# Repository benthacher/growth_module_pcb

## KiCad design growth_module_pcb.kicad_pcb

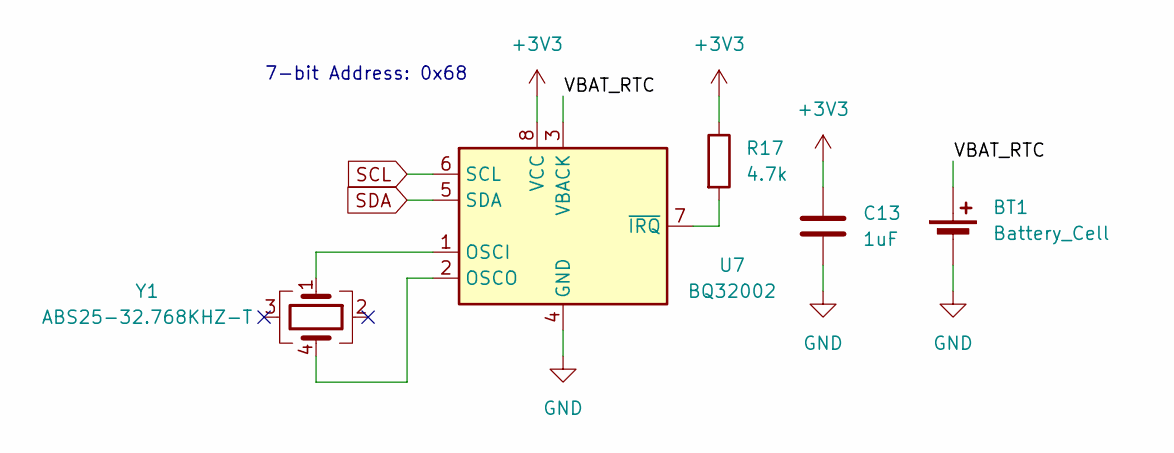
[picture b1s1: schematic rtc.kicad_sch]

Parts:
BT1: Battery_Cell; BatteryHolder_Keystone_3000_1x12mm
C13: 1uF; C_0603_1608Metric_Pad1.08x0.95mm_HandSolder
R17: 4.7k; R_0603_1608Metric_Pad0.98x0.95mm_HandSolder
U7: BQ32002; SOIC-8_3.9x4.9mm_P1.27mm
Y1: ABS25-32.768KHZ-T; Crystal_SMD_Abracon_ABS25-4Pin_8.0x3.8mm

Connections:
+3V3: C13.1, R17.1, U7.8 (VCC); also elsewhere on the board
/RTC/VBAT_RTC: BT1.1 (+), U7.3 (VBACK)
GND: BT1.2 (-), C13.2, U7.4 (GND); also elsewhere on the board
unnamed: U7.1 (OSCI), Y1.1
unnamed: U7.2 (OSCO), Y1.4
unnamed: R17.2, U7.7 (~IRQ)
SCL: U7.6 (SCL); also elsewhere on the board
SDA: U7.5 (SDA); also elsewhere on the board

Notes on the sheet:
7-bit Address: 0x68

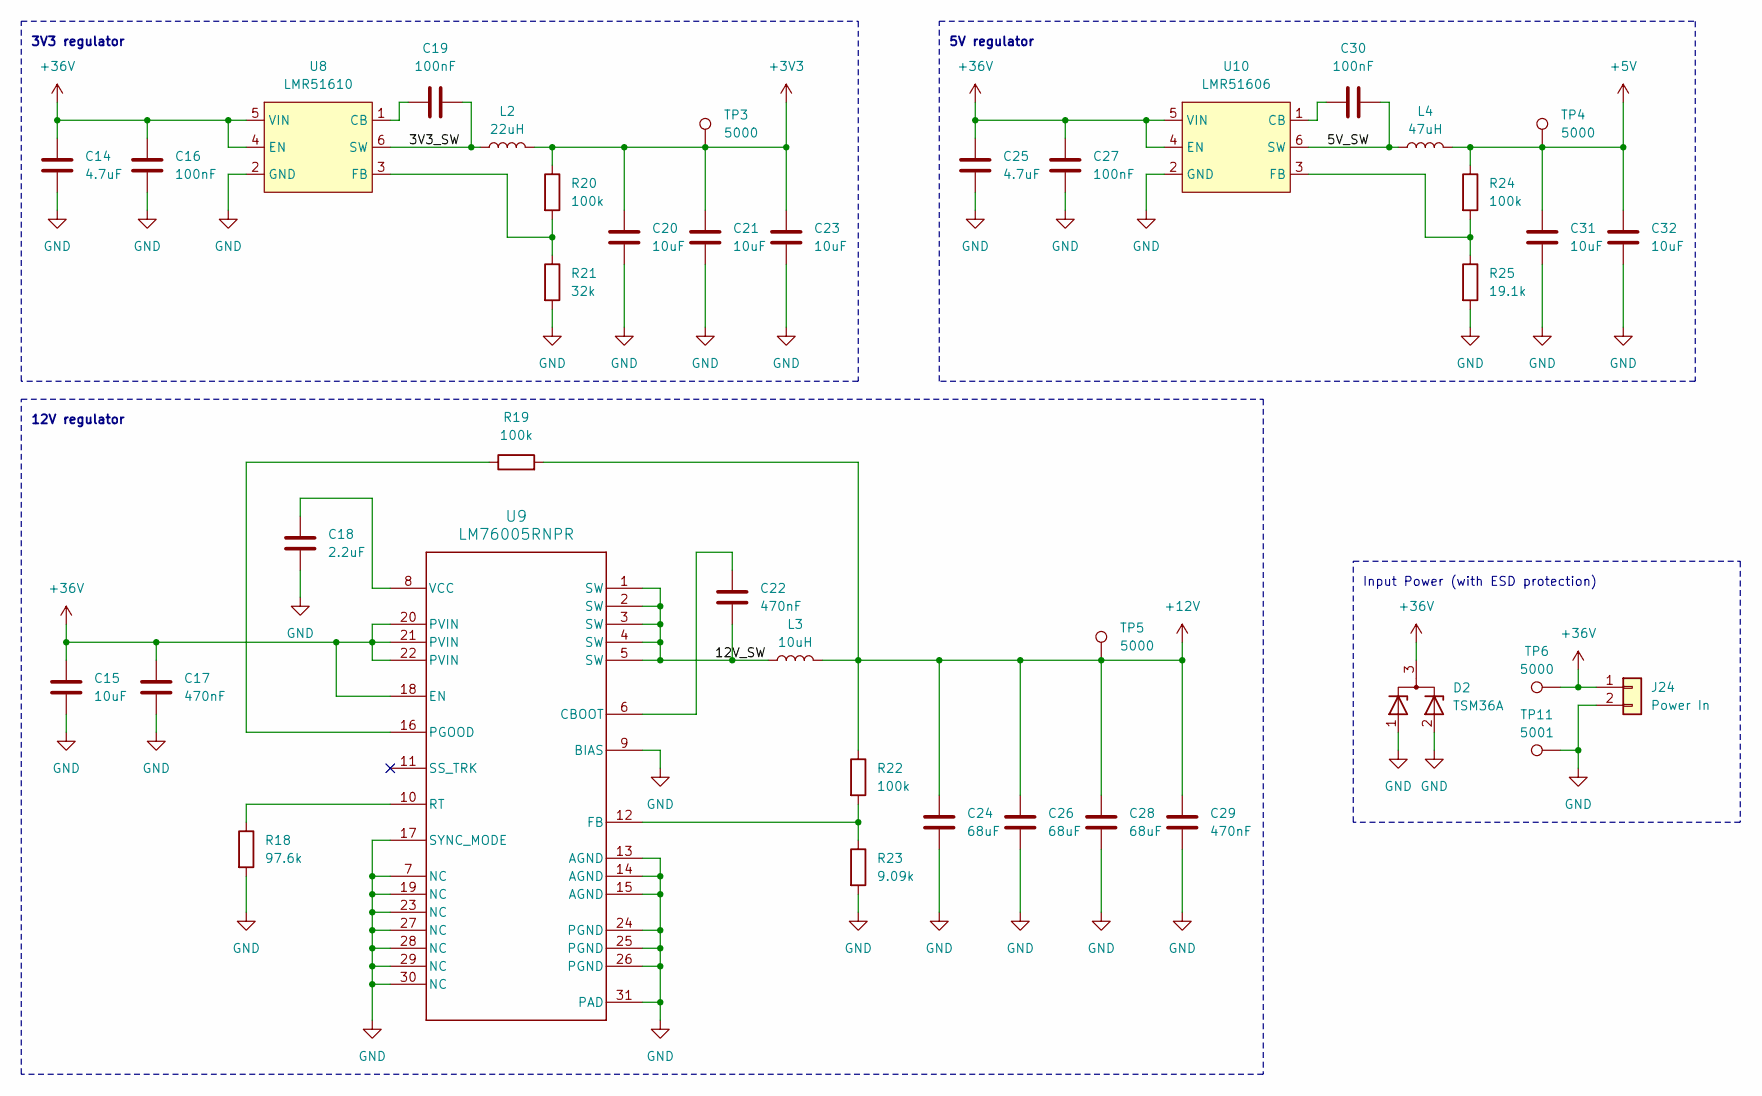
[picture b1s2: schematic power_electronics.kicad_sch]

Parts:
C14, C25: 4.7uF; C_2220_5750Metric_Pad1.97x5.40mm_HandSolder
C15: 10uF; C_1210_3225Metric_Pad1.33x2.70mm_HandSolder
C16, C19, C27, C30: 100nF; C_0603_1608Metric_Pad1.08x0.95mm_HandSolder
C17: 470nF; C_0805_2012Metric_Pad1.18x1.45mm_HandSolder
C18: 2.2uF; C_0603_1608Metric_Pad1.08x0.95mm_HandSolder
C20, C21, C23, C31, C32: 10uF; C_0805_2012Metric_Pad1.18x1.45mm_HandSolder
C22, C29: 470nF; C_0603_1608Metric_Pad1.08x0.95mm_HandSolder
C24, C26, C28: 68uF; CP_Elec_6.3x7.7
D2: TSM36A; SOT-23_Handsoldering
J24: Power In; JST_VH_S2P-VH_1x02_P3.96mm_Horizontal
L2: 22uH; SDR1006220ML
L3: 10uH; IND_BOURNS_SRP1270-M
L4: 47uH; SDR1006220ML
R18: 97.6k; R_0603_1608Metric_Pad0.98x0.95mm_HandSolder
R19, R20, R22, R24: 100k; R_0603_1608Metric_Pad0.98x0.95mm_HandSolder
R21: 32k; R_0603_1608Metric_Pad0.98x0.95mm_HandSolder
R23: 9.09k; R_0603_1608Metric_Pad0.98x0.95mm_HandSolder
R25: 19.1k; R_0603_1608Metric_Pad0.98x0.95mm_HandSolder
TP3, TP4, TP5, TP6: 5000; TestPoint_Keystone_5000-5004_Miniature
TP11: 5001; TestPoint_Keystone_5000-5004_Miniature
U8: LMR51610; LMR51610XDBVR
U9: LM76005RNPR; RNP0030A
U10: LMR51606; LMR51610XDBVR

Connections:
+3V3: C20.1, C21.1, C23.1, L2.2, R20.1, TP3.1; also elsewhere on the board
+5V: C31.1, C32.1, L4.2, R24.1, TP4.1; also elsewhere on the board
+12V: C24.1, C26.1, C28.1, C29.1, L3.2, R19.2, R22.1, TP5.1; also elsewhere on the board
+36V: C14.1, C15.1, C16.1, C17.1, C25.1, C27.1, D2.3 (A), J24.1, TP6.1, U8.4 (EN), U8.5 (VIN), U9.18 (EN), U9.20 (PVIN), U9.21 (PVIN), U9.22 (PVIN), U10.4 (EN), U10.5 (VIN); also elsewhere on the board
/Power electronics/3V3_SW: C19.2, L2.1, U8.6 (SW)
/Power electronics/5V_SW: C30.2, L4.1, U10.6 (SW)
/Power electronics/12V_SW: C22.2, L3.1, U9.1 (SW), U9.2 (SW), U9.3 (SW), U9.4 (SW), U9.5 (SW)
GND: C14.2, C15.2, C16.2, C17.2, C18.2, C20.2, C21.2, C23.2, C24.2, C25.2, C26.2, C27.2, C28.2, C29.2, C31.2, C32.2, D2.1 (K), D2.2 (K), J24.2, R18.2, R21.2, R23.2, R25.2, TP11.1, U8.2 (GND), U9.7 (NC), U9.9 (BIAS), U9.13 (AGND), U9.14 (AGND), U9.15 (AGND), U9.17 (SYNC_MODE), U9.19 (NC), U9.23 (NC), U9.24 (PGND), U9.25 (PGND), U9.26 (PGND), U9.27 (NC), U9.28 (NC), U9.29 (NC), U9.30 (NC), U9.31 (PAD), U10.2 (GND); also elsewhere on the board
unnamed: C19.1, U8.1 (CB)
unnamed: R20.2, R21.1, U8.3 (FB)
unnamed: C22.1, U9.6 (CBOOT)
unnamed: R22.2, R23.1, U9.12 (FB)
unnamed: R19.1, U9.16 (PGOOD)
unnamed: R18.1, U9.10 (RT)
unnamed: C18.1, U9.8 (VCC)
unnamed: C30.1, U10.1 (CB)
unnamed: R24.2, R25.1, U10.3 (FB)

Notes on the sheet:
Input Power (with ESD protection)
12V regulator
5V regulator
3V3 regulator

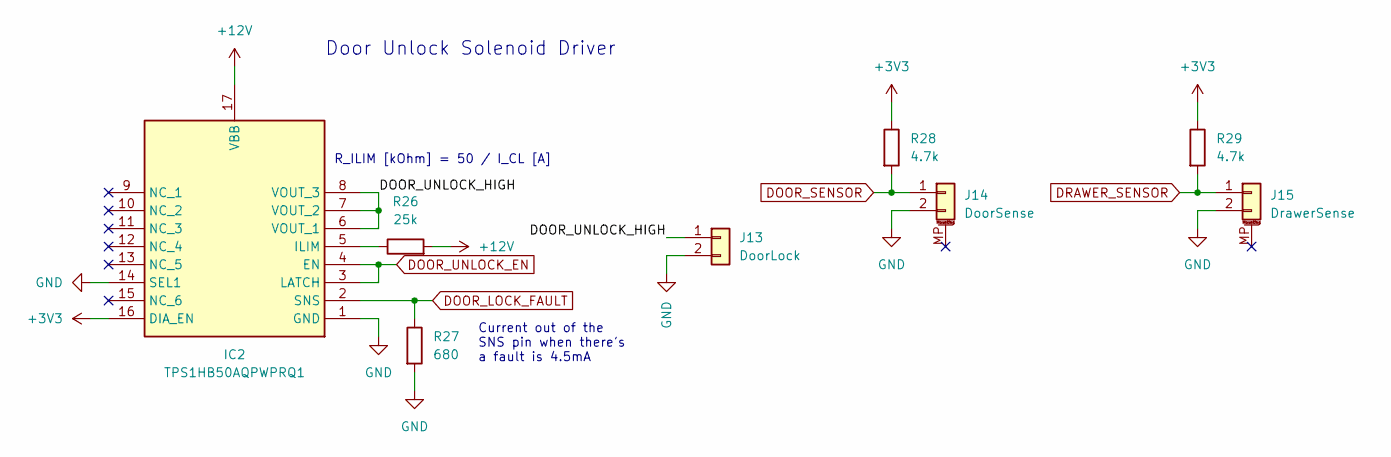
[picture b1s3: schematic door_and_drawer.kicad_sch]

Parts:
IC2: TPS1HB50AQPWPRQ1; HTSSOP-16-1EP_4.4x5mm_P0.65mm_EP3.4x5mm_Mask3x3mm_ThermalVi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; Manufacturer_Part_Number TPS1HB50AQPWPRQ1; Mouser Part Number 595-TPS1HB50AQPWPRQ1
J13: DoorLock; JST_XA_S02B-XASK-1_1x02_P2.50mm_Horizontal
J14: DoorSense; JST_SH_SM02B-SRSS-TB_1x02-1MP_P1.00mm_Horizontal
J15: DrawerSense; JST_SH_SM02B-SRSS-TB_1x02-1MP_P1.00mm_Horizontal
R26: 25k; R_0603_1608Metric_Pad0.98x0.95mm_HandSolder
R27: 680; R_0603_1608Metric_Pad0.98x0.95mm_HandSolder
R28, R29: 4.7k; R_0603_1608Metric_Pad0.98x0.95mm_HandSolder

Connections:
+3V3: IC2.16 (DIA_EN), R28.1, R29.1; also elsewhere on the board
+12V: IC2.17 (VBB), R26.2; also elsewhere on the board
/Door and Drawer/DOOR_UNLOCK_HIGH: IC2.6 (VOUT_1), IC2.7 (VOUT_2), IC2.8 (VOUT_3), J13.1
DOOR_LOCK_FAULT: IC2.2 (SNS), R27.1; also elsewhere on the board
DOOR_SENSOR: J14.1, R28.2; also elsewhere on the board
DOOR_UNLOCK_EN: IC2.3 (LATCH), IC2.4 (EN); also elsewhere on the board
DRAWER_SENSOR: J15.1, R29.2; also elsewhere on the board
GND: IC2.1 (GND), IC2.14 (SEL1), J13.2, J14.2, J15.2, R27.2; also elsewhere on the board
unnamed: IC2.5 (ILIM), R26.1

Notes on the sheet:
R_ILIM [kOhm] = 50 / I_CL [A]
Door Unlock Solenoid Driver
Current out of the SNS pin when there's a fault is 4.5mA

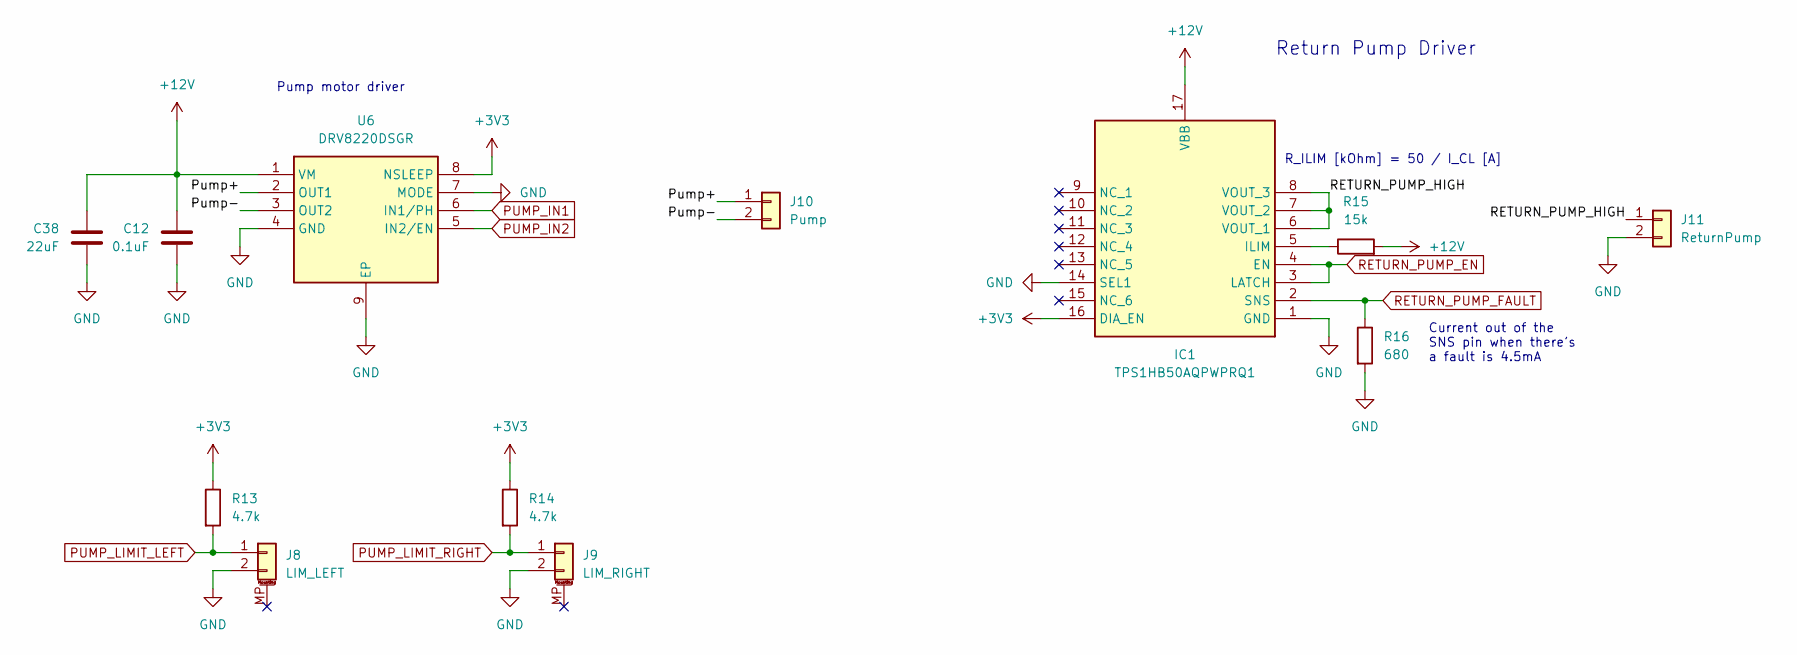
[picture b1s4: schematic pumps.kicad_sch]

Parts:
C12: 0.1uF; C_0603_1608Metric_Pad1.08x0.95mm_HandSolder
C38: 22uF; C_0805_2012Metric_Pad1.18x1.45mm_HandSolder
IC1: TPS1HB50AQPWPRQ1; HTSSOP-16-1EP_4.4x5mm_P0.65mm_EP3.4x5mm_Mask3x3mm_ThermalVi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; Manufacturer_Part_Number TPS1HB50AQPWPRQ1; Mouser Part Number 595-TPS1HB50AQPWPRQ1
J8: LIM_LEFT; JST_SH_SM02B-SRSS-TB_1x02-1MP_P1.00mm_Horizontal
J9: LIM_RIGHT; JST_SH_SM02B-SRSS-TB_1x02-1MP_P1.00mm_Horizontal
J10: Pump; JST_XA_S02B-XASK-1_1x02_P2.50mm_Horizontal
J11: ReturnPump; JST_XA_S02B-XASK-1_1x02_P2.50mm_Horizontal
R13, R14: 4.7k; R_0603_1608Metric_Pad0.98x0.95mm_HandSolder
R15: 15k; R_0603_1608Metric_Pad0.98x0.95mm_HandSolder
R16: 680; R_0603_1608Metric_Pad0.98x0.95mm_HandSolder
U6: DRV8220DSGR; SON50P200X200X80-9N; Manufacturer_Part_Number DRV8220DSGR; Mouser Part Number 595-DRV8220DSGR

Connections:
+3V3: IC1.16 (DIA_EN), R13.1, R14.1, U6.8 (NSLEEP); also elsewhere on the board
+12V: C12.1, C38.1, IC1.17 (VBB), R15.2, U6.1 (VM); also elsewhere on the board
/Pumps/Pump+: J10.1, U6.2 (OUT1)
/Pumps/Pump-: J10.2, U6.3 (OUT2)
/Pumps/RETURN_PUMP_HIGH: IC1.6 (VOUT_1), IC1.7 (VOUT_2), IC1.8 (VOUT_3), J11.1
GND: C12.2, C38.2, IC1.1 (GND), IC1.14 (SEL1), J8.2, J9.2, J11.2, R16.2, U6.4 (GND), U6.7 (MODE), U6.9 (EP); also elsewhere on the board
unnamed: IC1.5 (ILIM), R15.1
PUMP_IN1: U6.6 (IN1/PH); also elsewhere on the board
PUMP_IN2: U6.5 (IN2/EN); also elsewhere on the board
PUMP_LIMIT_LEFT: J8.1, R13.2; also elsewhere on the board
PUMP_LIMIT_RIGHT: J9.1, R14.2; also elsewhere on the board
RETURN_PUMP_EN: IC1.3 (LATCH), IC1.4 (EN); also elsewhere on the board
RETURN_PUMP_FAULT: IC1.2 (SNS), R16.1; also elsewhere on the board

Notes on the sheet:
R_ILIM [kOhm] = 50 / I_CL [A]
Current out of the SNS pin when there's a fault is 4.5mA
Return Pump Driver
Pump motor driver

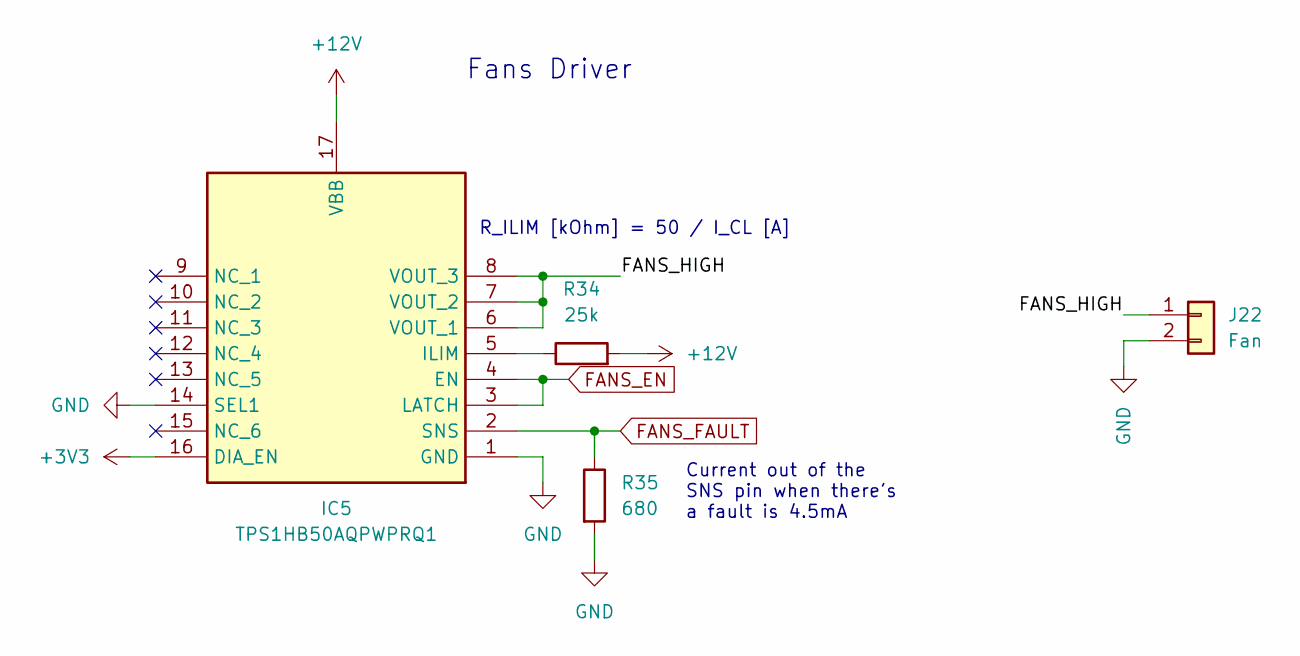
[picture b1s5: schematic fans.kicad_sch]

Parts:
IC5: TPS1HB50AQPWPRQ1; HTSSOP-16-1EP_4.4x5mm_P0.65mm_EP3.4x5mm_Mask3x3mm_ThermalVi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; Manufacturer_Part_Number TPS1HB50AQPWPRQ1; Mouser Part Number 595-TPS1HB50AQPWPRQ1
J22: Fan; JST_XA_S02B-XASK-1_1x02_P2.50mm_Horizontal
R34: 25k; R_0603_1608Metric_Pad0.98x0.95mm_HandSolder
R35: 680; R_0603_1608Metric_Pad0.98x0.95mm_HandSolder

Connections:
+3V3: IC5.16 (DIA_EN); also elsewhere on the board
+12V: IC5.17 (VBB), R34.2; also elsewhere on the board
/Fans/FANS_HIGH: IC5.6 (VOUT_1), IC5.7 (VOUT_2), IC5.8 (VOUT_3), J22.1
FANS_EN: IC5.3 (LATCH), IC5.4 (EN); also elsewhere on the board
FANS_FAULT: IC5.2 (SNS), R35.1; also elsewhere on the board
GND: IC5.1 (GND), IC5.14 (SEL1), J22.2, R35.2; also elsewhere on the board
unnamed: IC5.5 (ILIM), R34.1

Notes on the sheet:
R_ILIM [kOhm] = 50 / I_CL [A]
Current out of the SNS pin when there's a fault is 4.5mA
Fans Driver

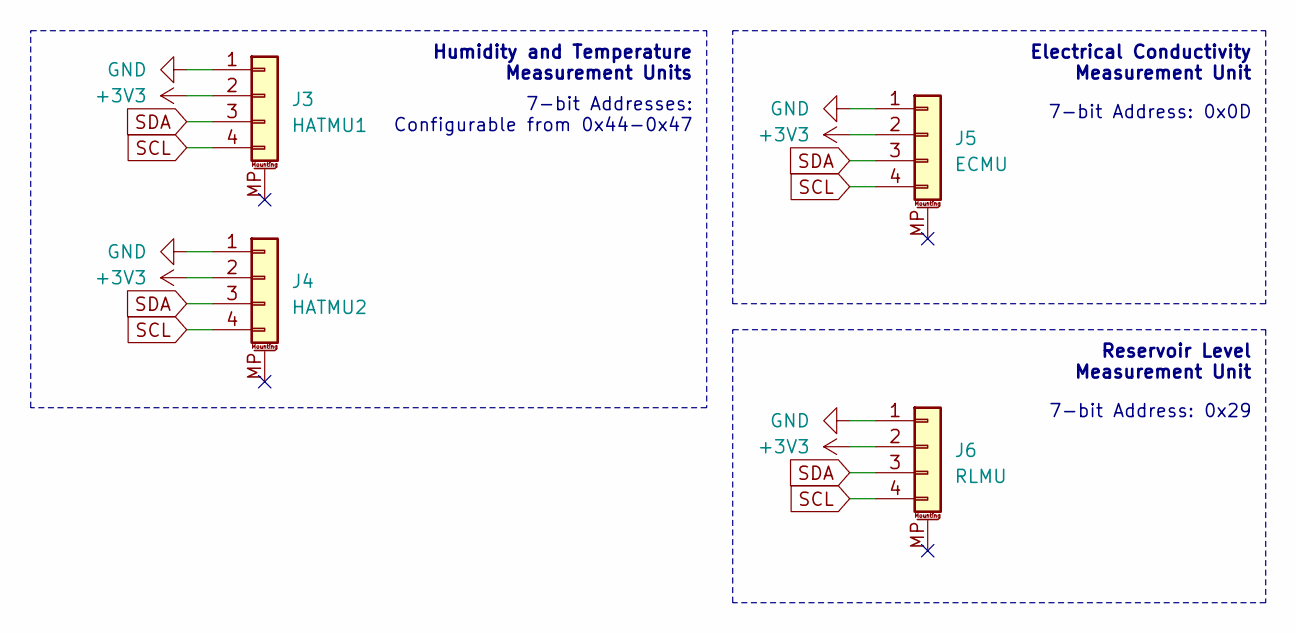
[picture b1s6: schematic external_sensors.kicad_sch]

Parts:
J3: HATMU1; JST_SH_SM04B-SRSS-TB_1x04-1MP_P1.00mm_Horizontal
J4: HATMU2; JST_SH_SM04B-SRSS-TB_1x04-1MP_P1.00mm_Horizontal
J5: ECMU; JST_SH_SM04B-SRSS-TB_1x04-1MP_P1.00mm_Horizontal
J6: RLMU; JST_SH_SM04B-SRSS-TB_1x04-1MP_P1.00mm_Horizontal

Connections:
+3V3: J3.2, J4.2, J5.2, J6.2; also elsewhere on the board
GND: J3.1, J4.1, J5.1, J6.1; also elsewhere on the board
SCL: J3.4, J4.4, J5.4, J6.4; also elsewhere on the board
SDA: J3.3, J4.3, J5.3, J6.3; also elsewhere on the board

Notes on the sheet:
Reservoir Level Measurement Unit
7-bit Addresses: Configurable from 0x44-0x47
Electrical Conductivity Measurement Unit
Humidity and Temperature Measurement Units
7-bit Address: 0x29
7-bit Address: 0x0D

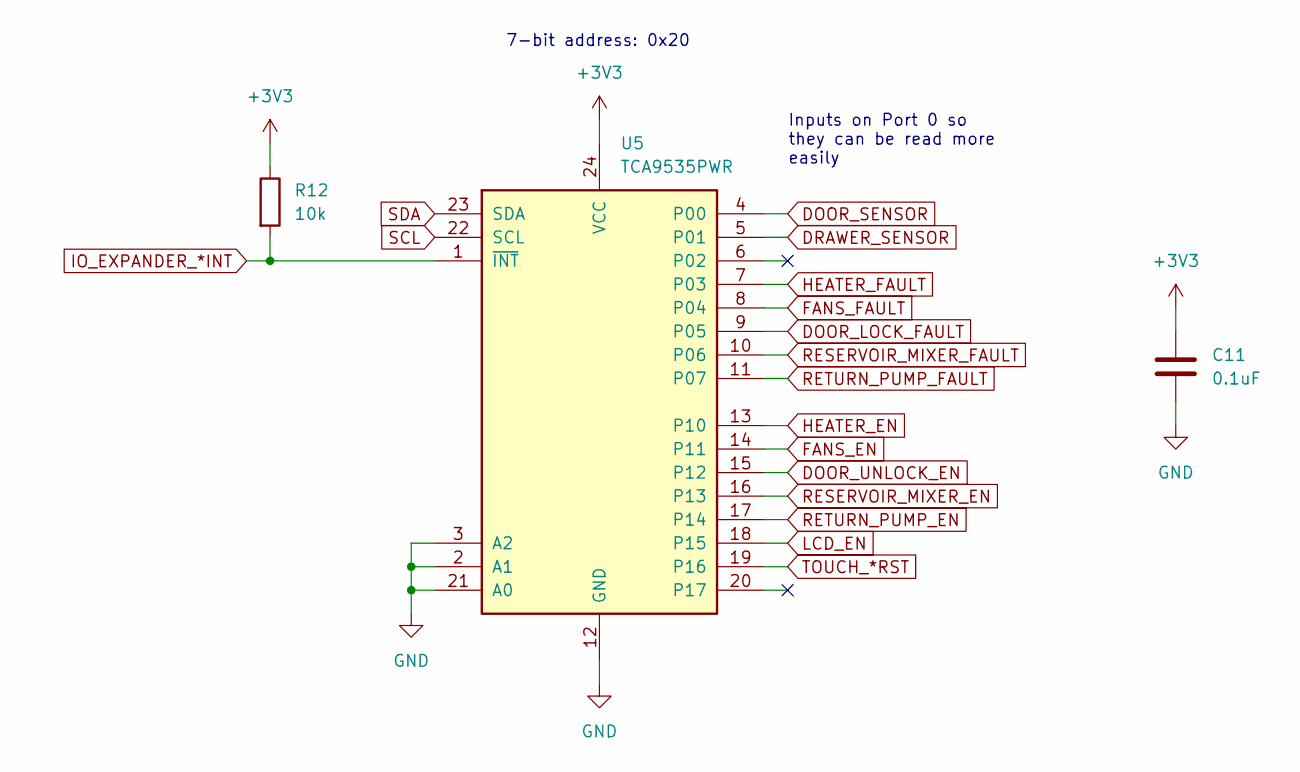
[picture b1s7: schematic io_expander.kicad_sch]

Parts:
C11: 0.1uF; C_0603_1608Metric_Pad1.08x0.95mm_HandSolder
R12: 10k; R_0603_1608Metric_Pad0.98x0.95mm_HandSolder
U5: TCA9535PWR; TSSOP-24_4.4x7.8mm_P0.65mm

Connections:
+3V3: C11.1, R12.1, U5.24 (VCC); also elsewhere on the board
DOOR_LOCK_FAULT: U5.9 (P05); also elsewhere on the board
DOOR_SENSOR: U5.4 (P00); also elsewhere on the board
DOOR_UNLOCK_EN: U5.15 (P12); also elsewhere on the board
DRAWER_SENSOR: U5.5 (P01); also elsewhere on the board
FANS_EN: U5.14 (P11); also elsewhere on the board
FANS_FAULT: U5.8 (P04); also elsewhere on the board
GND: C11.2, U5.2 (A1), U5.3 (A2), U5.12 (GND), U5.21 (A0); also elsewhere on the board
HEATER_EN: U5.13 (P10); also elsewhere on the board
HEATER_FAULT: U5.7 (P03); also elsewhere on the board
IO_EXPANDER_*INT: R12.2, U5.1 (~INT); also elsewhere on the board
LCD_EN: U5.18 (P15); also elsewhere on the board
RESERVOIR_MIXER_EN: U5.16 (P13); also elsewhere on the board
RESERVOIR_MIXER_FAULT: U5.10 (P06); also elsewhere on the board
RETURN_PUMP_EN: U5.17 (P14); also elsewhere on the board
RETURN_PUMP_FAULT: U5.11 (P07); also elsewhere on the board
SCL: U5.22 (SCL); also elsewhere on the board
SDA: U5.23 (SDA); also elsewhere on the board
TOUCH_*RST: U5.19 (P16); also elsewhere on the board

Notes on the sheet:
7-bit address: 0x20
Inputs on Port 0 so they can be read more easily

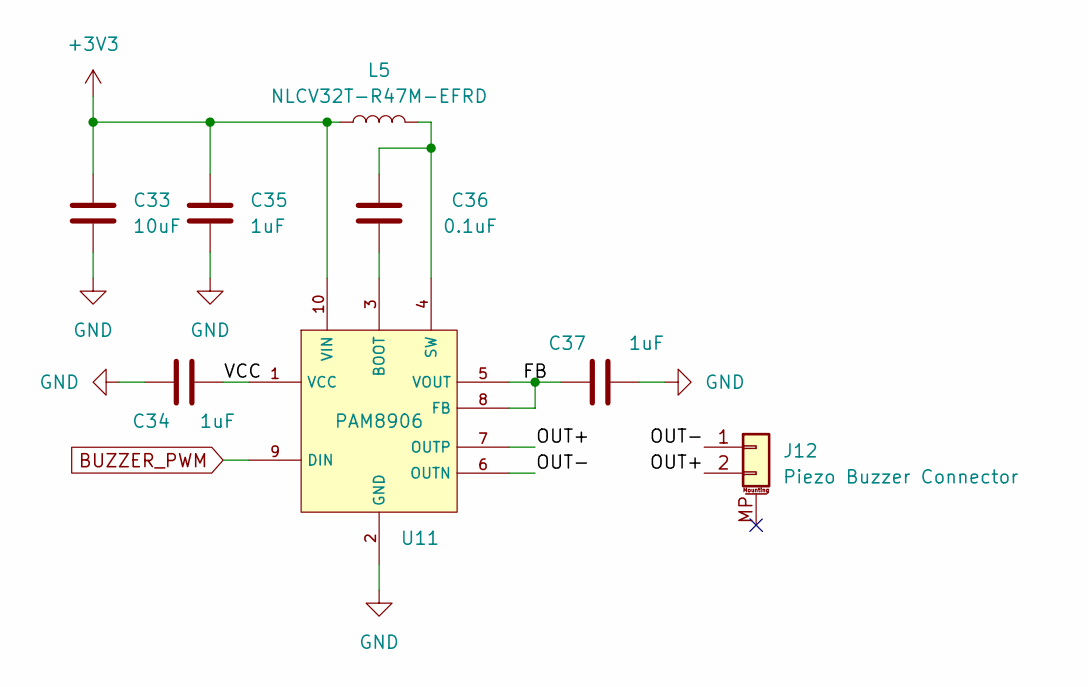
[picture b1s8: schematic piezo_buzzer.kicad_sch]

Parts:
C33: 10uF; C_0805_2012Metric_Pad1.18x1.45mm_HandSolder
C34, C35, C37: 1uF; C_0603_1608Metric_Pad1.08x0.95mm_HandSolder
C36: 0.1uF; C_0603_1608Metric_Pad1.08x0.95mm_HandSolder
J12: Piezo Buzzer Connector; JST_PH_S2B-PH-SM4-TB_1x02-1MP_P2.00mm_Horizontal
L5: NLCV32T-R47M-EFRD; L_1210_3225Metric_Pad1.42x2.65mm_HandSolder
U11: PAM8906; MSOP-10_3x3mm_P0.5mm

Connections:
+3V3: C33.2, C35.2, L5.1, U11.10 (VIN); also elsewhere on the board
/Piezo buzzer/FB: C37.1, U11.5 (VOUT), U11.8 (FB)
/Piezo buzzer/OUT+: J12.2, U11.7 (OUTP)
/Piezo buzzer/OUT-: J12.1, U11.6 (OUTN)
/Piezo buzzer/VCC: C34.2, U11.1 (VCC)
BUZZER_PWM: U11.9 (DIN); also elsewhere on the board
GND: C33.1, C34.1, C35.1, C37.2, U11.2 (GND); also elsewhere on the board
unnamed: C36.1, U11.3 (BOOT)
unnamed: C36.2, L5.2, U11.4 (SW)

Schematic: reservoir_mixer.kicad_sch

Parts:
IC4: TPS1HB50AQPWPRQ1; HTSSOP-16-1EP_4.4x5mm_P0.65mm_EP3.4x5mm_Mask3x3mm_ThermalVi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; Manufacturer_Part_Number TPS1HB50AQPWPRQ1; Mouser Part Number 595-TPS1HB50AQPWPRQ1
J21: Mixer; JST_XA_S02B-XASK-1_1x02_P2.50mm_Horizontal
R32: 15k; R_0603_1608Metric_Pad0.98x0.95mm_HandSolder
R33: 680; R_0603_1608Metric_Pad0.98x0.95mm_HandSolder

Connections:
+3V3: IC4.16 (DIA_EN); also elsewhere on the board
+12V: IC4.17 (VBB), R32.2; also elsewhere on the board
/Reservoir Mixer/MIXER_HIGH: IC4.6 (VOUT_1), IC4.7 (VOUT_2), IC4.8 (VOUT_3), J21.1
GND: IC4.1 (GND), IC4.14 (SEL1), J21.2, R33.2; also elsewhere on the board
unnamed: IC4.5 (ILIM), R32.1
RESERVOIR_MIXER_EN: IC4.3 (LATCH), IC4.4 (EN); also elsewhere on the board
RESERVOIR_MIXER_FAULT: IC4.2 (SNS), R33.1; also elsewhere on the board

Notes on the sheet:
R_ILIM [kOhm] = 50 / I_CL [A]
Reservoir Mixer Driver
Current out of the SNS pin when there's a fault is 4.5mA

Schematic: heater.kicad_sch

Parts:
IC3: TPS1HB50AQPWPRQ1; HTSSOP-16-1EP_4.4x5mm_P0.65mm_EP3.4x5mm_Mask3x3mm_ThermalVi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; Manufacturer_Part_Number TPS1HB50AQPWPRQ1; Mouser Part Number 595-TPS1HB50AQPWPRQ1
J16: Heater; JST_VH_S2P-VH_1x02_P3.96mm_Horizontal
R30: 12k; R_0603_1608Metric_Pad0.98x0.95mm_HandSolder
R31: 680; R_0603_1608Metric_Pad0.98x0.95mm_HandSolder

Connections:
+3V3: IC3.16 (DIA_EN); also elsewhere on the board
+36V: IC3.17 (VBB), R30.2; also elsewhere on the board
/Heater/HEATER_HIGH: IC3.6 (VOUT_1), IC3.7 (VOUT_2), IC3.8 (VOUT_3), J16.1
GND: IC3.1 (GND), IC3.14 (SEL1), J16.2, R31.2; also elsewhere on the board
HEATER_EN: IC3.3 (LATCH), IC3.4 (EN); also elsewhere on the board
HEATER_FAULT: IC3.2 (SNS), R31.1; also elsewhere on the board
unnamed: IC3.5 (ILIM), R30.1

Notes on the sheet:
Current out of the SNS pin when there's a fault is 4.5mA
Heater Driver
R_ILIM [kOhm] = 50 / I_CL [A]

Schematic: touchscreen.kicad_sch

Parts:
C7: 10uF; C_0603_1608Metric_Pad1.08x0.95mm_HandSolder
C8: 0.1uF; C_0603_1608Metric_Pad1.08x0.95mm_HandSolder
C9: 22uF; C_0603_1608Metric_Pad1.08x0.95mm_HandSolder
C10: 2.2uF; C_1210_3225Metric_Pad1.33x2.70mm_HandSolder
D1: BAS3010B03WE6327HTSA1; D_SOD-323_HandSoldering
J7: Conn_01x40_MountingPin; ER-CON40HT-1
L1: 10uH; L_1210_3225Metric_Pad1.42x2.65mm_HandSolder
R11: 20; R_0805_2012Metric_Pad1.20x1.40mm_HandSolder
R36: 22; R_0603_1608Metric_Pad0.98x0.95mm_HandSolder
U4: PT4110; SOT-89-5_Handsoldering

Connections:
+3V3: C7.1, C8.1, C9.1, J7.4, L1.1, U4.1 (IN); also elsewhere on the board
/Touchscreen/LED+: C10.1, D1.1 (K), J7.2
/Touchscreen/LED-: C10.2, J7.1, R11.1, U4.4 (FB)
/Touchscreen/SW: D1.2 (A), L1.2, U4.5 (SW)
GND: C7.2, C8.2, C9.2, J7.3, J7.5, J7.6, J7.7, J7.8, J7.9, J7.10, J7.11, J7.12, J7.21, J7.22, J7.23, J7.24, J7.25, J7.26, J7.27, J7.28, J7.29, J7.32, J7.33, J7.36, R11.2, U4.2 (GND); also elsewhere on the board
LCD_BACKLIGHT_PWM: U4.3 (EN); also elsewhere on the board
LCD_D0: J7.13; also elsewhere on the board
LCD_D1: J7.14; also elsewhere on the board
LCD_D2: J7.15; also elsewhere on the board
LCD_D3: J7.16; also elsewhere on the board
LCD_D4: J7.17; also elsewhere on the board
LCD_D5: J7.18; also elsewhere on the board
LCD_D6: J7.19; also elsewhere on the board
LCD_D7: J7.20; also elsewhere on the board
LCD_DE: J7.34; also elsewhere on the board
LCD_EN: J7.31; also elsewhere on the board
LCD_PCLK: R36.1; also elsewhere on the board
unnamed: J7.30, R36.2
SCL: J7.39; also elsewhere on the board
SDA: J7.40; also elsewhere on the board
TOUCH_*INT: J7.37; also elsewhere on the board
TOUCH_*RST: J7.38; also elsewhere on the board

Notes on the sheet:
Touch IC 7-bit address: 0x38

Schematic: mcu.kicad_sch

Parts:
C1: 1uF; C_0603_1608Metric_Pad1.08x0.95mm_HandSolder
C2: 10uF; C_0603_1608Metric_Pad1.08x0.95mm_HandSolder
C3, C4, C39, C40: 0.1uF; C_0603_1608Metric_Pad1.08x0.95mm_HandSolder
J1: USB_C_Receptacle_USB2.0_14P; USB_C_Receptacle_HRO_TYPE-C-31-M-12
R1: 10k; R_0603_1608Metric_Pad0.98x0.95mm_HandSolder
R2, R3: 2.2k; R_0603_1608Metric_Pad0.98x0.95mm_HandSolder
R4, R5: 5.1k; R_0603_1608Metric_Pad0.98x0.95mm_HandSolder
SW1, SW2: RST; SW_SPST_CK_RS282G05A3
TP1, TP7: 5002; TestPoint_Keystone_5000-5004_Miniature
TP13: 5001; TestPoint_Keystone_5000-5004_Miniature
U1: ESP32-S3-WROOM-1U-N16R8; XCVR_ESP32-S3-WROOM-2-N32R8V; PARTREV 1.0
U2: USBLC6-2SC6; SOT-23-6

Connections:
+3V3: C2.1, C3.1, R1.1, R2.1, R3.1, U1.2 (3V3); also elsewhere on the board
/MCU/IO0: C40.1, SW2.2, U1.27 (IO0)
BUZZER_PWM: U1.19 (IO11); also elsewhere on the board
GND: C1.2, C2.2, C3.2, C4.2, C39.2, C40.2, J1.A1 (GND), J1.A12 (GND), J1.B1 (GND), J1.B12 (GND), J1.S1 (SHIELD), R4.2, R5.2, SW1.1, SW2.1, TP13.1, U1.1 (GND), U1.40 (GND), U1.41 (GND), U2.2 (GND); also elsewhere on the board
GROW_LIGHT_PWM: U1.21 (IO13); also elsewhere on the board
IO_EXPANDER_*INT: U1.22 (IO14); also elsewhere on the board
LCD_BACKLIGHT_PWM: U1.20 (IO12); also elsewhere on the board
LCD_D0: U1.4 (IO4); also elsewhere on the board
LCD_D1: U1.5 (IO5); also elsewhere on the board
LCD_D2: U1.6 (IO6); also elsewhere on the board
LCD_D3: U1.7 (IO7); also elsewhere on the board
LCD_D4: U1.8 (IO15); also elsewhere on the board
LCD_D5: U1.9 (IO16); also elsewhere on the board
LCD_D6: U1.10 (IO17); also elsewhere on the board
LCD_D7: U1.11 (IO18); also elsewhere on the board
LCD_DE: U1.15 (IO3); also elsewhere on the board
LCD_PCLK: U1.12 (IO8); also elsewhere on the board
unnamed: J1.A5 (CC1), R4.1
unnamed: J1.B5 (CC2), R5.1
unnamed: C1.1, C39.1, R1.2, SW1.2, U1.3 (EN)
PUMP_IN1: U1.17 (IO9); also elsewhere on the board
PUMP_IN2: U1.18 (IO10); also elsewhere on the board
PUMP_LIMIT_LEFT: U1.39 (IO1); also elsewhere on the board
PUMP_LIMIT_RIGHT: U1.38 (IO2); also elsewhere on the board
SCL: R3.2, TP7.1, U1.25 (IO48); also elsewhere on the board
SDA: R2.2, TP1.1, U1.24 (IO47); also elsewhere on the board
TOUCH_*INT: U1.36 (RXD0); also elsewhere on the board
USB_JTAG_D+: U1.14 (IO20), U2.6 (I/O1)
USB_JTAG_D-: U1.13 (IO19), U2.4 (I/O2)
USB_JTAG_RAW_D+: J1.A6 (D+), J1.B6 (D+), U2.1 (I/O1)
USB_JTAG_RAW_D-: J1.A7 (D-), J1.B7 (D-), U2.3 (I/O2)
USB_PHY_OE: U1.33 (IO40); also elsewhere on the board
USB_PHY_RCV: U1.23 (IO21); also elsewhere on the board
USB_PHY_VM: U1.34 (IO41); also elsewhere on the board
USB_PHY_VMO: U1.31 (IO38); also elsewhere on the board
USB_PHY_VP: U1.35 (IO42); also elsewhere on the board
USB_PHY_VPO: U1.32 (IO39); also elsewhere on the board
VUSB: C4.1, J1.A4 (VBUS), J1.A9 (VBUS), J1.B4 (VBUS), J1.B9 (VBUS), U2.5 (VBUS)

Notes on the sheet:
I2C devices: Peripheral │ 7-bit Address ───────────┼────────────── HATMU (2) │ 0x44-0x47 ECMU │ 0x0D RLMU │ 0x29 IO Expander│ 0x20 RTC │ 0x68 Touch Panel│ 0x38
GPIO44
Boot circuit needed (tested on devkit)

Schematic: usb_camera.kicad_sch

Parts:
C5, C6: 0.1uF; C_0603_1608Metric_Pad1.08x0.95mm_HandSolder
J2: UE27AC54100; AMPHENOL_UE27AC54100; PARTREV E
R6, R7: 33; R_0603_1608Metric_Pad0.98x0.95mm_HandSolder
R8, R9: 15k; R_0603_1608Metric_Pad0.98x0.95mm_HandSolder
U3: TUSB1106RTZR; Texas_Instruments-TUSB1106RTZR-Manufacturer_Recommended

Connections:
+3V3: C5.1, C6.1, U3.7 (VCC), U3.8 (SPEED), U3.13 (VREG), U3.14 (VCC); also elsewhere on the board
+5V: J2.1 (VCC); also elsewhere on the board
/USB Camera/D+: R6.1, U3.10 (D+)
/USB Camera/D-: R7.1, U3.9 (D-)
GND: C5.2, C6.2, J2.4 (GND), R8.2, R9.2, U3.5 (SUSPND), U3.6 (GND), U3.16 (SOFTCON), U3.17 (EPAD); also elsewhere on the board
USB_PHY_D+: J2.3 (D+), R6.2, R8.1
USB_PHY_D-: J2.2 (D-), R7.2, R9.1
USB_PHY_OE: U3.1 (*OE); also elsewhere on the board
USB_PHY_RCV: U3.2 (RCV); also elsewhere on the board
USB_PHY_VM: U3.4 (VM); also elsewhere on the board
USB_PHY_VMO: U3.12 (VMO); also elsewhere on the board
USB_PHY_VP: U3.3 (VP); also elsewhere on the board
USB_PHY_VPO: U3.11 (VPO); also elsewhere on the board

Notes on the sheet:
Drive SPEED pin HIGH to enable full speed USB
Drive SUSPEND pin LOW disables lower power mode
Camera Connector
SOFTCON = LOW: Don't use software connection

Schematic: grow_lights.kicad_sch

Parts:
J23: Conn_01x03; JST_VH_S3P-VH_1x03_P3.96mm_Horizontal

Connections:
+36V: J23.1; also elsewhere on the board
GND: J23.3; also elsewhere on the board
GROW_LIGHT_PWM: J23.2; also elsewhere on the board

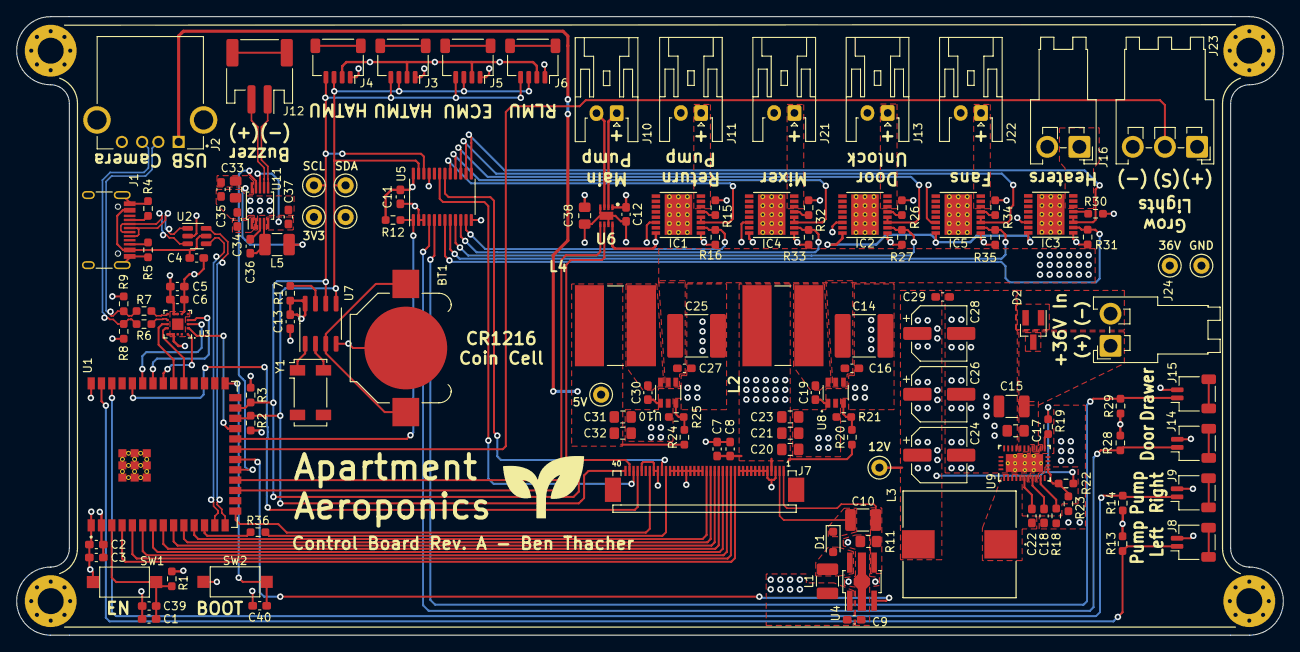
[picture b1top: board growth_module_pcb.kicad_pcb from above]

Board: 4 copper layers, 156.2 x 76.2 mm, 130 parts (0 on the bottom side), 97 nets.

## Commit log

2024-05-28 Initial Commit (file dump)
